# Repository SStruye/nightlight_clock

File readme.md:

# dimmable nightlight + clock using ESP12F(ESP8266)
This PCB design was an idea for a night light in combination with a clock. I found an old 4x40 LCD panel to use as display.
# PCB desing
- for the dimmable light i used a triac dimmer circuit.
- To save pins i used a multiplexer for the LCD.
- I also added a header that can be used for a rotary encoder and a header that can be used for an I2C temperature sensor or something else using I2C.

# software
- I had to edit the arduino liquidcrystal-I2C library to accomodate for the LCD using two LCD drivers. 1 for the top 2 rows and one for the bottom 2 rows. If i hadn't used a multiplexer
this wouldn't have been necessary.
- DMC40457_clock is a library i created to handle te logic behind the displaying of characters on to the lcd.
- clock_software.ino is the arduino sketch that runs on the ESP12F.

## result

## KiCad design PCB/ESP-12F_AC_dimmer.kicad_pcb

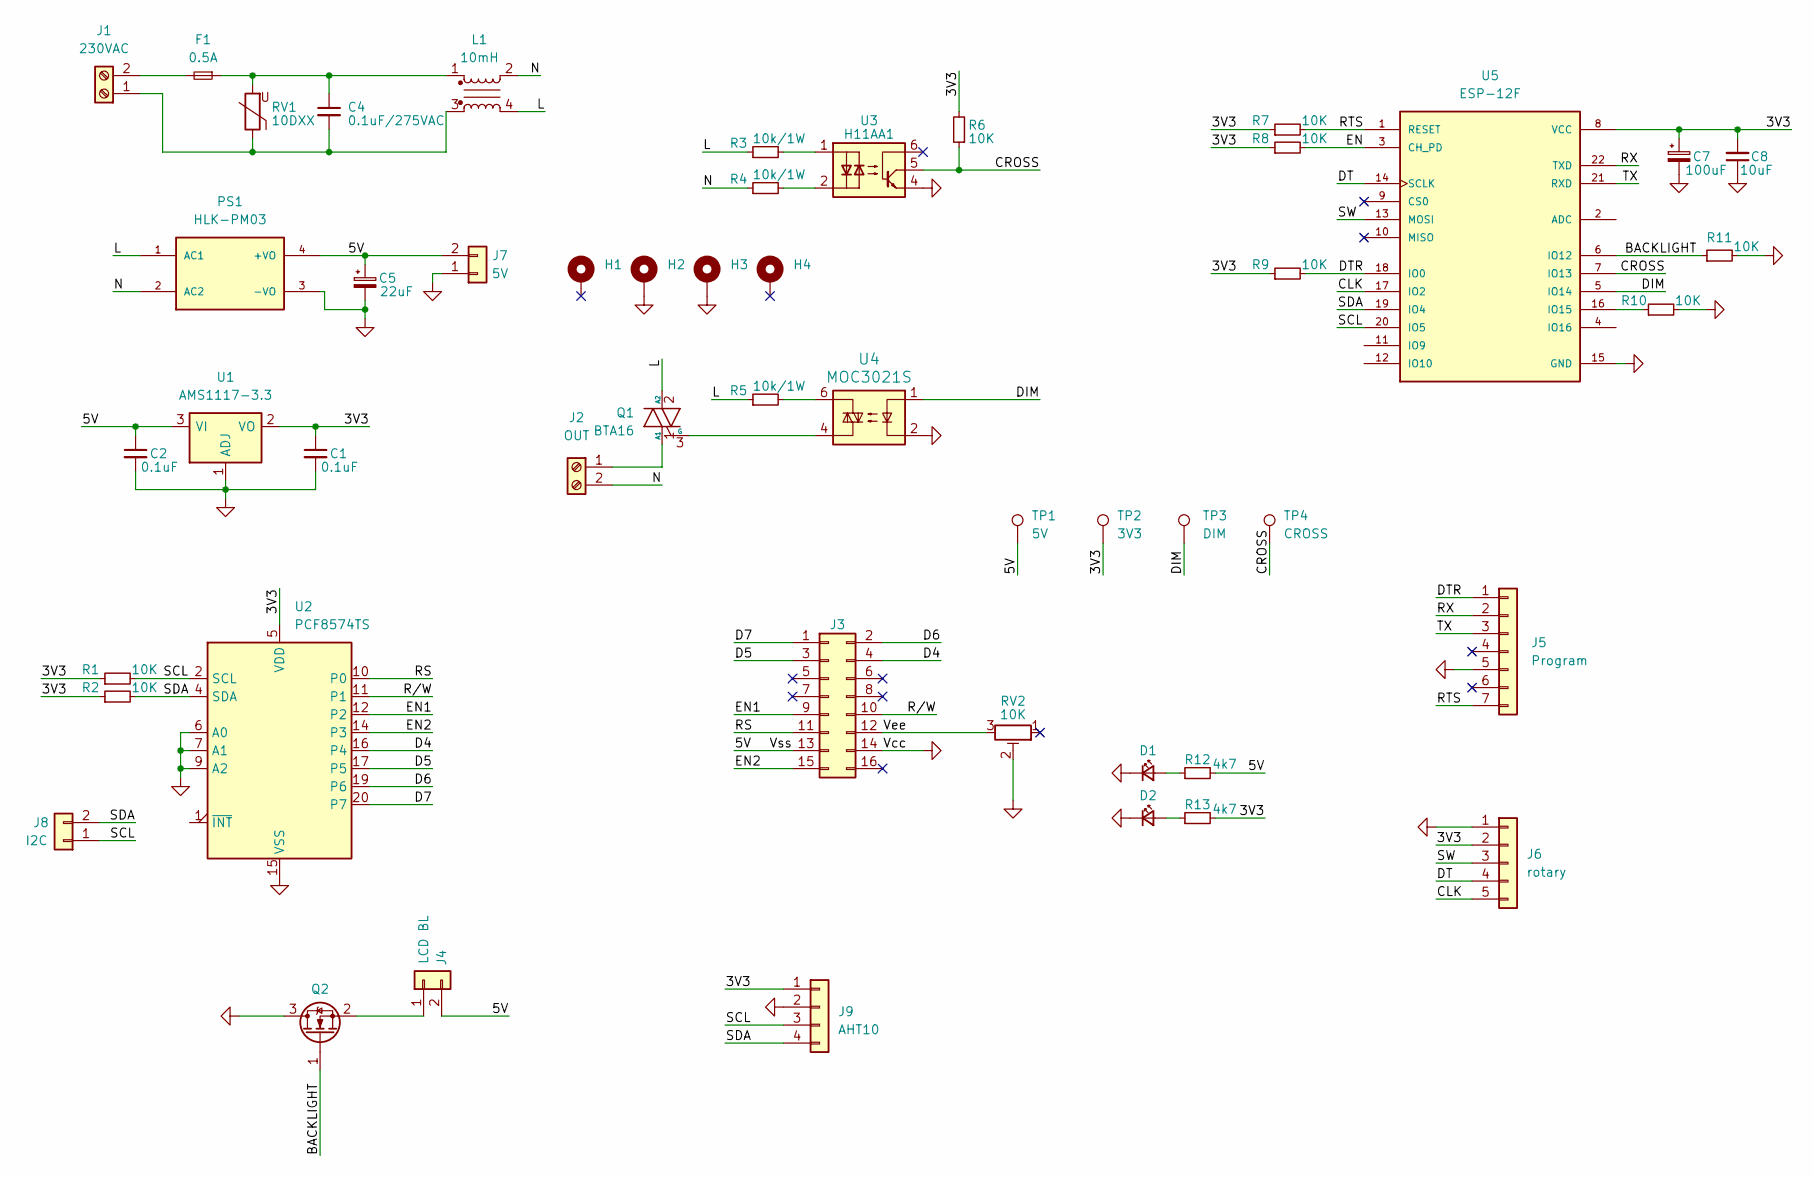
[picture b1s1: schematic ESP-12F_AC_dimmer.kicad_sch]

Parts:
C1, C2: 0.1uF; C_0805_2012Metric
C4: 0.1uF/275VAC; C_Rect_L16.5mm_W6.0mm_P15.00mm_MKT
C5: 22uF; CP_Elec_5x5.4
C7: 100uF; CP_Elec_5x5.4
C8: 10uF; C_0603_1608Metric
D1, D2: LED_Small; LED_0603_1608Metric
F1: 0.5A; BLX-A
H1, H2, H3, H4: MountingHole_Pad; MountingHole_3.2mm_M3_Pad_Via
J1: 230VAC; TerminalBlock_Phoenix_PT-1,5-2-5.0-H_1x02_P5.00mm_Horizontal
J2: OUT; TerminalBlock_Phoenix_PT-1,5-2-5.0-H_1x02_P5.00mm_Horizontal
J3: LCD; IDC-Header_2x08_P2.54mm_Vertical
J4: LCD BL; PinSocket_1x02_P2.54mm_Vertical
J5: Program; PinSocket_1x07_P2.54mm_Vertical
J6: rotary; PinSocket_1x05_P2.54mm_Vertical
J7: 5V; PinSocket_1x02_P2.54mm_Vertical
J8: I2C; PinSocket_1x02_P2.54mm_Vertical
J9: AHT10; PinSocket_1x04_P2.54mm_Vertical
L1: 10mH; choke
PS1: HLK-PM03; CONV_HLK-PM03
Q1: BTA16; TO-220-3_Vertical_2
Q2: K1459; TO-220-3_Vertical
R1, R2, R6, R7, R8, R9, R10, R11: 10K; R_0603_1608Metric
R3, R4, R5: 10k/1W; R_2512_6332Metric
R12, R13: 4k7; R_0603_1608Metric
RV1: 10DXX; RV_Disc_D9mm_W3.3mm_P5mm
RV2: 10K; Potentiometer_Bourns_3296W_Vertical
TP1: 5V; TestPoint_Pad_D1.0mm
TP2: 3V3; TestPoint_Pad_D1.0mm
TP3: DIM; TestPoint_Pad_D1.0mm
TP4: CROSS; TestPoint_Pad_D1.0mm
U1: AMS1117-3.3; SOT-223-3_TabPin2
U2: PCF8574TS; SSOP-20_4.4x6.5mm_P0.65mm
U3: H11AA1; MOC3021S
U4: MOC3021S
U5: ESP-12F; XCVR_ESP8266-12E_ESP-12E

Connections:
/3V3: C1.1, C7.1, C8.2, J6.2, J9.1, R1.1, R2.1, R6.2, R7.1, R8.1, R9.1, R13.2, TP2.1, U1.2 (VO), U2.5 (VDD), U5.8 (VCC)
/5V: C2.1, C5.1, J3.13, J4.2, J7.2, PS1.4 (+VO), R12.2, TP1.1, U1.3 (VI)
/BACKLIGHT: Q2.1 (G), R11.1, U5.6 (IO12)
/CLK: J6.5, U5.17 (IO2)
/CROSS: R6.1, TP4.1, U3.5, U5.7 (IO13)
/D4: J3.4, U2.16 (P4)
/D5: J3.3, U2.17 (P5)
/D6: J3.2, U2.19 (P6)
/D7: J3.1, U2.20 (P7)
/DIM: TP3.1, U4.1, U5.5 (IO14)
/DT: J6.4, U5.14 (SCLK)
/DTR: J5.1, R9.2, U5.18 (IO0)
/EN: R8.2, U5.3 (CH_PD)
/EN1: J3.9, U2.12 (P2)
/EN2: J3.15, U2.14 (P3)
/L: L1.4, PS1.1 (AC1), Q1.2 (A2), R3.1, R5.1
/N: J2.2, L1.2, PS1.2 (AC2), R4.1
/RS: J3.11, U2.10 (P0)
/RTS: J5.7, R7.2, U5.1 (RESET)
/RX: J5.2, U5.22 (TXD)
/R/W: J3.10, U2.11 (P1)
/SCL: J8.1, J9.3, R1.2, U2.2 (SCL), U5.20 (IO5)
/SDA: J8.2, J9.4, R2.2, U2.4 (SDA), U5.19 (IO4)
/SW: J6.3, U5.13 (MOSI)
/TX: J5.3, U5.21 (RXD)
/Vee: J3.12, RV2.3
GND: C1.2, C2.2, C5.2, C7.2, C8.1, D1.1 (K), D2.1 (K), H2.1, H3.1, J3.14, J5.5, J6.1, J7.1, J9.2, PS1.3 (-VO), Q2.3 (D), R10.2, R11.2, RV2.2, U1.1 (ADJ), U2.6 (A0), U2.7 (A1), U2.9 (A2), U2.15 (VSS), U3.4, U4.2, U5.15 (GND)
unnamed: C4.1, F1.1, L1.1, RV1.2
unnamed: D1.2 (A), R12.1
unnamed: D2.2 (A), R13.1
unnamed: C4.2, J1.1, L1.3, RV1.1
unnamed: F1.2, J1.2
unnamed: J2.1, Q1.1 (A1)
unnamed: J4.1, Q2.2 (S)
unnamed: Q1.3 (G), U4.4
unnamed: R3.2, U3.1
unnamed: R4.2, U3.2
unnamed: R5.2, U4.6
unnamed: R10.1, U5.16 (IO15)

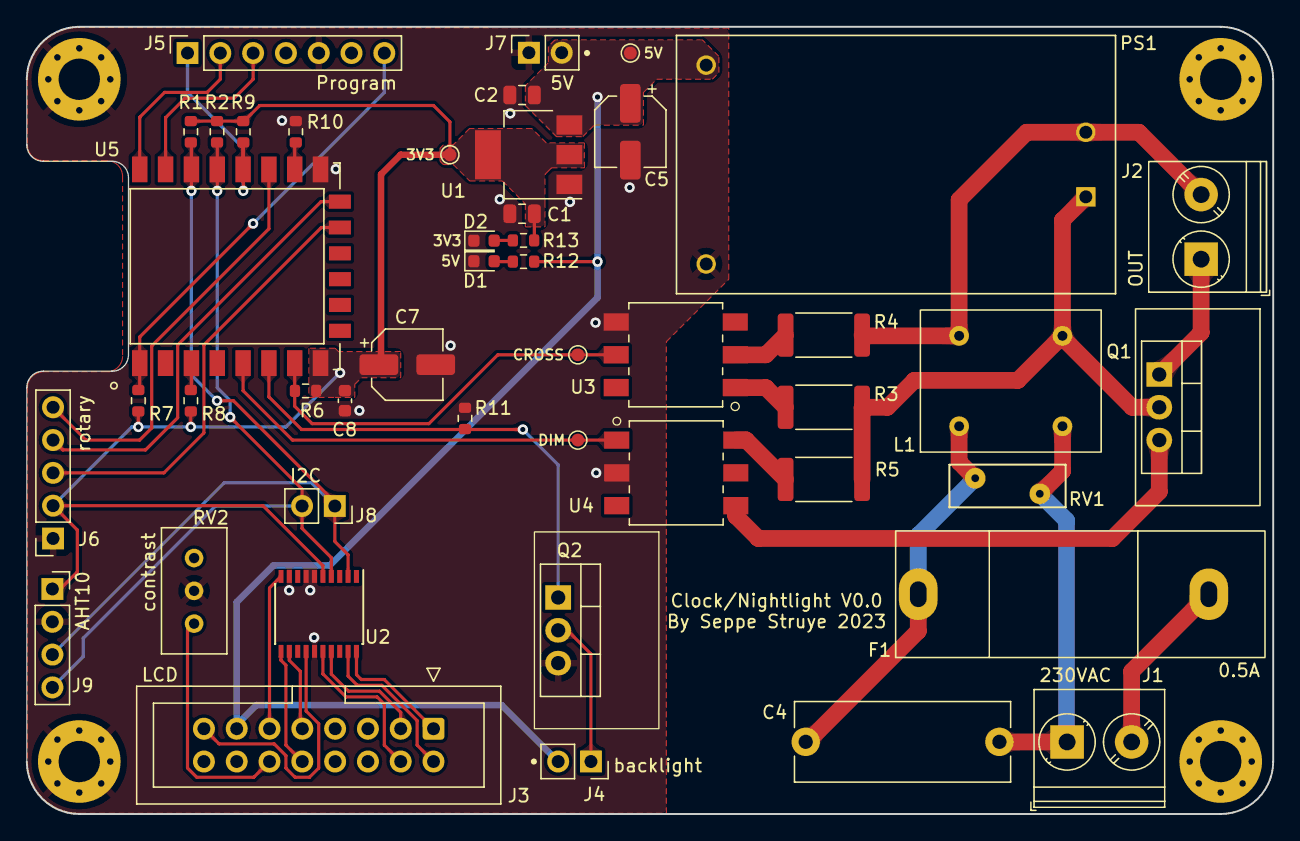
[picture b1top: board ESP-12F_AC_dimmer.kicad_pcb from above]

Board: 2 copper layers, 96.5 x 61.0 mm, 50 parts (0 on the bottom side), 39 nets.

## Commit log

2023-06-04 Create x
2023-06-04 edited liquidcrystal I2C
2023-06-04 clock display logic
